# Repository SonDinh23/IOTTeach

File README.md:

# IOTTeach

<div align="center">

### Modular IoT Learning & Test Kit

<sub>IOTTeach v1.0 — Top side (above) · Bottom side (below)</sub>

<br/><br/>

</div>

---

## Table of Contents

| Section | Description |
|---------|-------------|
| About | Overview and intent |
| Hardware Overview | Technical summary |
| Key Features | Highlights and educational notes |
| Block Diagram | System block diagram |
| Getting Started | Quick start and assembly checklist |
| Lab Scenarios | Suggested exercises by level |
| License | License guidance |

---

## About

IOTTeach is a detachable plug-in kit designed for hands-on learning, quick hardware validation, and classroom labs. It exposes common peripherals (relays, RGB/status LEDs, buzzer) and standard 2.54 mm headers for power, analog, and digital lines so students and developers can prototype with any MCU or SBC without soldering a custom shield.

Design philosophy: Bring Your Own MCU — connect any microcontroller (ESP32, STM32, Arduino, Raspberry Pi Pico, etc.) using Dupont wires.

---

## Hardware Overview

| Component | Detail |
|:--------:|:------|
| Power | DC jack (DC-005) + terminal block → TPS54202 buck converter → 3.3V/5V rail |
| GPIO Headers | Digital 1×10 · Digital 1×8 · Analog 1×6 · Power header (pitch 2.54 mm) |
| LED Indicators | 2× WS2812B RGB, discrete status LEDs (green/yellow/red) |
| Audio | Piezo buzzer (CMT-8530S-SMT), PWM capable |
| Relays | 2× Omron G5NB SPST relays, driven via SS8050 transistors |
| Protection | SS34 Schottky diodes for flyback, decoupling capacitors and input protection |
| Project Files | KiCad project and production outputs under `hardware/IOT1_V1.0/production/` |

### Core Components (summary)

• TPS54202DDC — Buck converter (3.3V, up to ~2A)

• WS2812B (×2) — Addressable RGB LEDs for visual feedback

• Omron G5NB Relays (×2) — SPST relays for switching experiments (observe safety limits)

• CMT-8530S-SMT — Piezo buzzer for audible signals

• SS8050 (×3) — NPN transistors as relay drivers

• SS34 (×4) — Schottky diodes for flyback/protection

---

## Key Features

### Modular & MCU-Agnostic

- Plug-and-play design: wire any MCU to the headers — no soldering required.
- Standard 2.54 mm pitch makes connecting and swapping modules fast and reliable.

### Education-Focused Layout

- Clear, labeled headers and wide component spacing for easy probing with oscilloscopes and logic analyzers.
- Progressive learning path: LEDs → switches → buzzer → relays → RGB, enabling stepwise lab exercises.

### Fabrication-Ready

- Complete production artifacts included: BOM, pick-and-place, netlist and KiCad project files.
- Files are in `hardware/IOT1_V1.0/production/` for easy handoff to PCB fabs and assemblers.

---

## Block Diagram

```
                              ┌─────────────────────────────────────┐
                              │          IOTTeach Board             │
                              └─────────────────────────────────────┘
                                              │
        ┌───────────────────────────────────────────────────────────────────┐
        │                                                                   │
        ▼                                                                   ▼
┌───────────────┐                                               ┌───────────────┐
│  POWER INPUT  │                                               │   MCU SIDE    │
│───────────────│                                               │───────────────│
│ • DC Jack     │                                               │ • Digital I/O │
│ • Terminal    │──► TPS54202 ──► 3.3V/5V Rail ──►             │ • Analog In   │
│   Block       │       Buck                                    │ • Power       │
└───────────────┘                                               └───────┬───────┘
                                                                        │
        ┌───────────────────────────────────────────────────────────────┘
        │
        ▼
┌─────────────────────────────────────────────────────────────────────────────┐
│                              PERIPHERALS                                     │
├─────────────────┬─────────────────┬─────────────────┬───────────────────────┤
│   VISUAL        │   AUDIO         │   ACTUATORS     │   INPUTS              │
├─────────────────┼─────────────────┼─────────────────┼───────────────────────┤
│ • 2× WS2812B    │ • Piezo Buzzer  │ • 2× SPST Relay │ • 2× Tactile Switch   │
│ • Status LEDs   │   (PWM tone)    │   (5A/250VAC)   │                       │
│                 │                 │ • SS34 Flyback  │                       │
└─────────────────┴─────────────────┴─────────────────┴───────────────────────┘
```

---

## Getting Started

### Prerequisites

- KiCad 7+ to view or edit the PCB project
- Any MCU board (ESP32, Arduino, STM32 Nucleo, Raspberry Pi Pico, etc.)
- Dupont jumper wires (Female-Female or Male-Female)

### Quick Start

```powershell
# Clone repository
git clone https://github.com/SonDinh23/IOTTeach.git
cd IOTTeach

# Open the KiCad project:
# File → Open Project → hardware/IOT1_V1.0/IOT1_V1.0.kicad_pro
```

### Recommended Assembly Order

1. Power stage: TPS54202, inductor, input/output capacitors, SS34 diodes
2. Install pin headers (all GPIO/power headers)
3. Passive components (resistors, caps)
4. Semiconductors (transistors, diodes, LEDs)
5. Modules and larger components (relays, buzzer, WS2812B)
6. Connectors and switches (DC jack, terminal blocks)

### First Power-On Checklist

- Verify no short between VCC and GND before powering
- Apply input power via DC jack (7–12 V recommended)
- Measure output rail (3.3V or 5V depending on configuration)
- Confirm power indicator LED lights up
- Connect MCU and run a basic LED blink test

---

## Lab Scenarios (Suggested Exercises)

### Level 1 — Beginner

- LED Blink: control a status LED (digital output)
- Button Read: read a tactile switch (digital input, pull-up)
- Buzzer Tone: generate tones using PWM (basic PWM)

### Level 2 — Intermediate

- RGB Effects: drive WS2812B for color patterns (NeoPixel protocol)
- Relay Timer: implement a timed relay control routine (timers/state machine)
- LED Patterns: create multi-LED sequences and animations (arrays/loops)

### Level 3 — Advanced

- Alarm System: integrate buzzer, RGB, and relay for a simulated alarm
- Power Profiling: measure board current under different loads (instrumentation)
- Remote Control: connect an MCU with Wi-Fi/BLE to control relays (networking)

---

## License

This project is presented as Open Hardware. Please add a specific license (for example, CERN-OHL, TAPR-OHL, or CC-BY-SA) to the repository before distributing manufacturing files or derivative works.

---

## Thanks

Thank you for exploring IOTTeach. Contributions, documentation improvements, and lab material suggestions are welcome — open an issue or submit a pull request.

<div align="center">

**[Back to Top](#iotteach)**

</div>

| Tính năng | Mô tả |
|-----------|-------|
| **MCU Agnostic** | Tương thích ESP32, STM32, Arduino, Raspberry Pi Pico, v.v. |
| **Plug & Play** | Kết nối nhanh qua dây Dupont, không cần hàn |
| **Header chuẩn** | Pitch 2.54mm phổ biến, dễ tìm phụ kiện |

### 📚 Education-Focused

| Tính năng | Mô tả |
|-----------|-------|
| **Clear Layout** | Component spacing rộng, dễ đo đạc oscilloscope |
| **Labeled Headers** | Đánh dấu rõ ràng chức năng từng chân |
| **Gradual Learning** | Từ LED → Switch → Buzzer → Relay → RGB |

### �icing Fabrication-Ready

| Tài liệu | Đường dẫn |
|----------|-----------|
| **Schematic** | `hardware/IOT1_V1.0/IOT1_V1.0.kicad_sch` |
| **PCB Layout** | `hardware/IOT1_V1.0/IOT1_V1.0.kicad_pcb` |
| **3D Model** | `hardware/IOT1_V1.0/IOT1_V1.0.step` |
| **BOM** | `hardware/IOT1_V1.0/production/bom.csv` |
| **Pick & Place** | `hardware/IOT1_V1.0/production/positions.csv` |

---

## 📊 Block Diagram

```
                              ┌─────────────────────────────────────┐
                              │          IOTTeach Board             │
                              └─────────────────────────────────────┘
                                              │
        ┌───────────────────────────────────────────────────────────────────┐
        │                                                                   │
        ▼                                                                   ▼
┌───────────────┐                                               ┌───────────────┐
│  POWER INPUT  │                                               │   MCU SIDE    │
│───────────────│                                               │───────────────│
│ • DC Jack     │                                               │ • Digital I/O │
│ • Terminal    │──► TPS54202 ──► 3.3V/5V Rail ──►             │ • Analog In   │
│   Block       │       Buck                                    │ • Power       │
└───────────────┘                                               └───────┬───────┘
                                                                        │
        ┌───────────────────────────────────────────────────────────────┘
        │
        ▼
┌─────────────────────────────────────────────────────────────────────────────┐
│                              PERIPHERALS                                     │
├─────────────────┬─────────────────┬─────────────────┬───────────────────────┤
│   💡 VISUAL     │   🔊 AUDIO      │   ⚙️ ACTUATOR   │   🎛️ INPUT            │
├─────────────────┼─────────────────┼─────────────────┼───────────────────────┤
│ • 2× WS2812B    │ • Piezo Buzzer  │ • 2× SPST Relay │ • 2× Tactile Switch   │
│ • 2× LED Green  │   (PWM tone)    │   (5A/250VAC)   │                       │
│ • 1× LED Yellow │                 │ • SS34 Flyback  │                       │
│ • 3× LED Red    │                 │                 │                       │
└─────────────────┴─────────────────┴─────────────────┴───────────────────────┘
```

---

## 🚀 Getting Started

### Prerequisites

- **KiCad 7+** để xem/chỉnh sửa thiết kế
- **MCU board** bất kỳ (ESP32, Arduino Uno, STM32 Nucleo, etc.)
- **Dây Dupont** Female-Female hoặc Male-Female

### Quick Start

```bash
# 1. Clone repository
git clone https://github.com/SonDinh23/IOTTeach.git
cd IOTTeach

# 2. Mở project KiCad
# File → Open Project → hardware/IOT1_V1.0/IOT1_V1.0.kicad_pro
```

### Assembly Order (Khuyến nghị)

| Bước | Thành phần | Ghi chú |
|:----:|------------|---------|
| 1️⃣ | **Power Stage** | TPS54202, inductor L1, capacitors, SS34 diodes |
| 2️⃣ | **Headers** | Tất cả pin headers (J1-J14) |
| 3️⃣ | **Passives** | Resistors, capacitors còn lại |
| 4️⃣ | **Semiconductors** | Transistors SS8050, LEDs |
| 5️⃣ | **Modules** | Relays, buzzer, WS2812B |
| 6️⃣ | **Connectors** | DC jack, terminal blocks, switches |

### First Power-On Checklist

- [ ] Kiểm tra ngắn mạch giữa VCC-GND trước khi cấp nguồn
- [ ] Cấp nguồn qua DC jack (7-12V recommended)
- [ ] Đo điện áp output rail (3.3V hoặc 5V tùy config)
- [ ] LED power indicator sáng
- [ ] Kết nối MCU và test blink LED

---

## 🧪 Lab Scenarios

### 🟢 Level 1: Beginner

| Bài lab | Mô tả | Kỹ năng |
|---------|-------|---------|
| **LED Blink** | Điều khiển LED đơn ON/OFF | Digital Output |
| **Button Read** | Đọc trạng thái nút nhấn | Digital Input, Pull-up |
| **Buzzer Tone** | Tạo âm thanh với tần số khác nhau | PWM basics |

### 🟡 Level 2: Intermediate

| Bài lab | Mô tả | Kỹ năng |
|---------|-------|---------|
| **RGB Rainbow** | Hiệu ứng cầu vồng với WS2812B | NeoPixel protocol |
| **Relay Timer** | Bật/tắt relay theo thời gian | Timing, State machine |
| **Multi-LED Pattern** | Đèn chạy đuổi, hiệu ứng | Arrays, Loops |

### 🔴 Level 3: Advanced

| Bài lab | Mô tả | Kỹ năng |
|---------|-------|---------|
| **Smart Alarm** | Hệ thống báo động: buzzer + LED + relay | System integration |
| **Power Profiling** | Đo dòng tiêu thụ ở các chế độ | Instrumentation |
| **IoT Control** | Điều khiển relay qua WiFi/BLE | Networking |

---

## 📜 License

Dự án này được phát hành dưới dạng **Open Hardware**.

> ⚠️ Vui lòng thêm license cụ thể (CERN-OHL, TAPR-OHL, hoặc CC-BY-SA) trước khi phân phối thiết kế.

---

## 🙏 Thanks

Cảm ơn bạn đã quan tâm đến **IOTTeach**!

Mọi góp ý về thiết kế, tài liệu hướng dẫn, hoặc ý tưởng bài thực hành đều được hoan nghênh.

<div align="center">

**[⬆ Back to Top](#iotteach)**

</div>

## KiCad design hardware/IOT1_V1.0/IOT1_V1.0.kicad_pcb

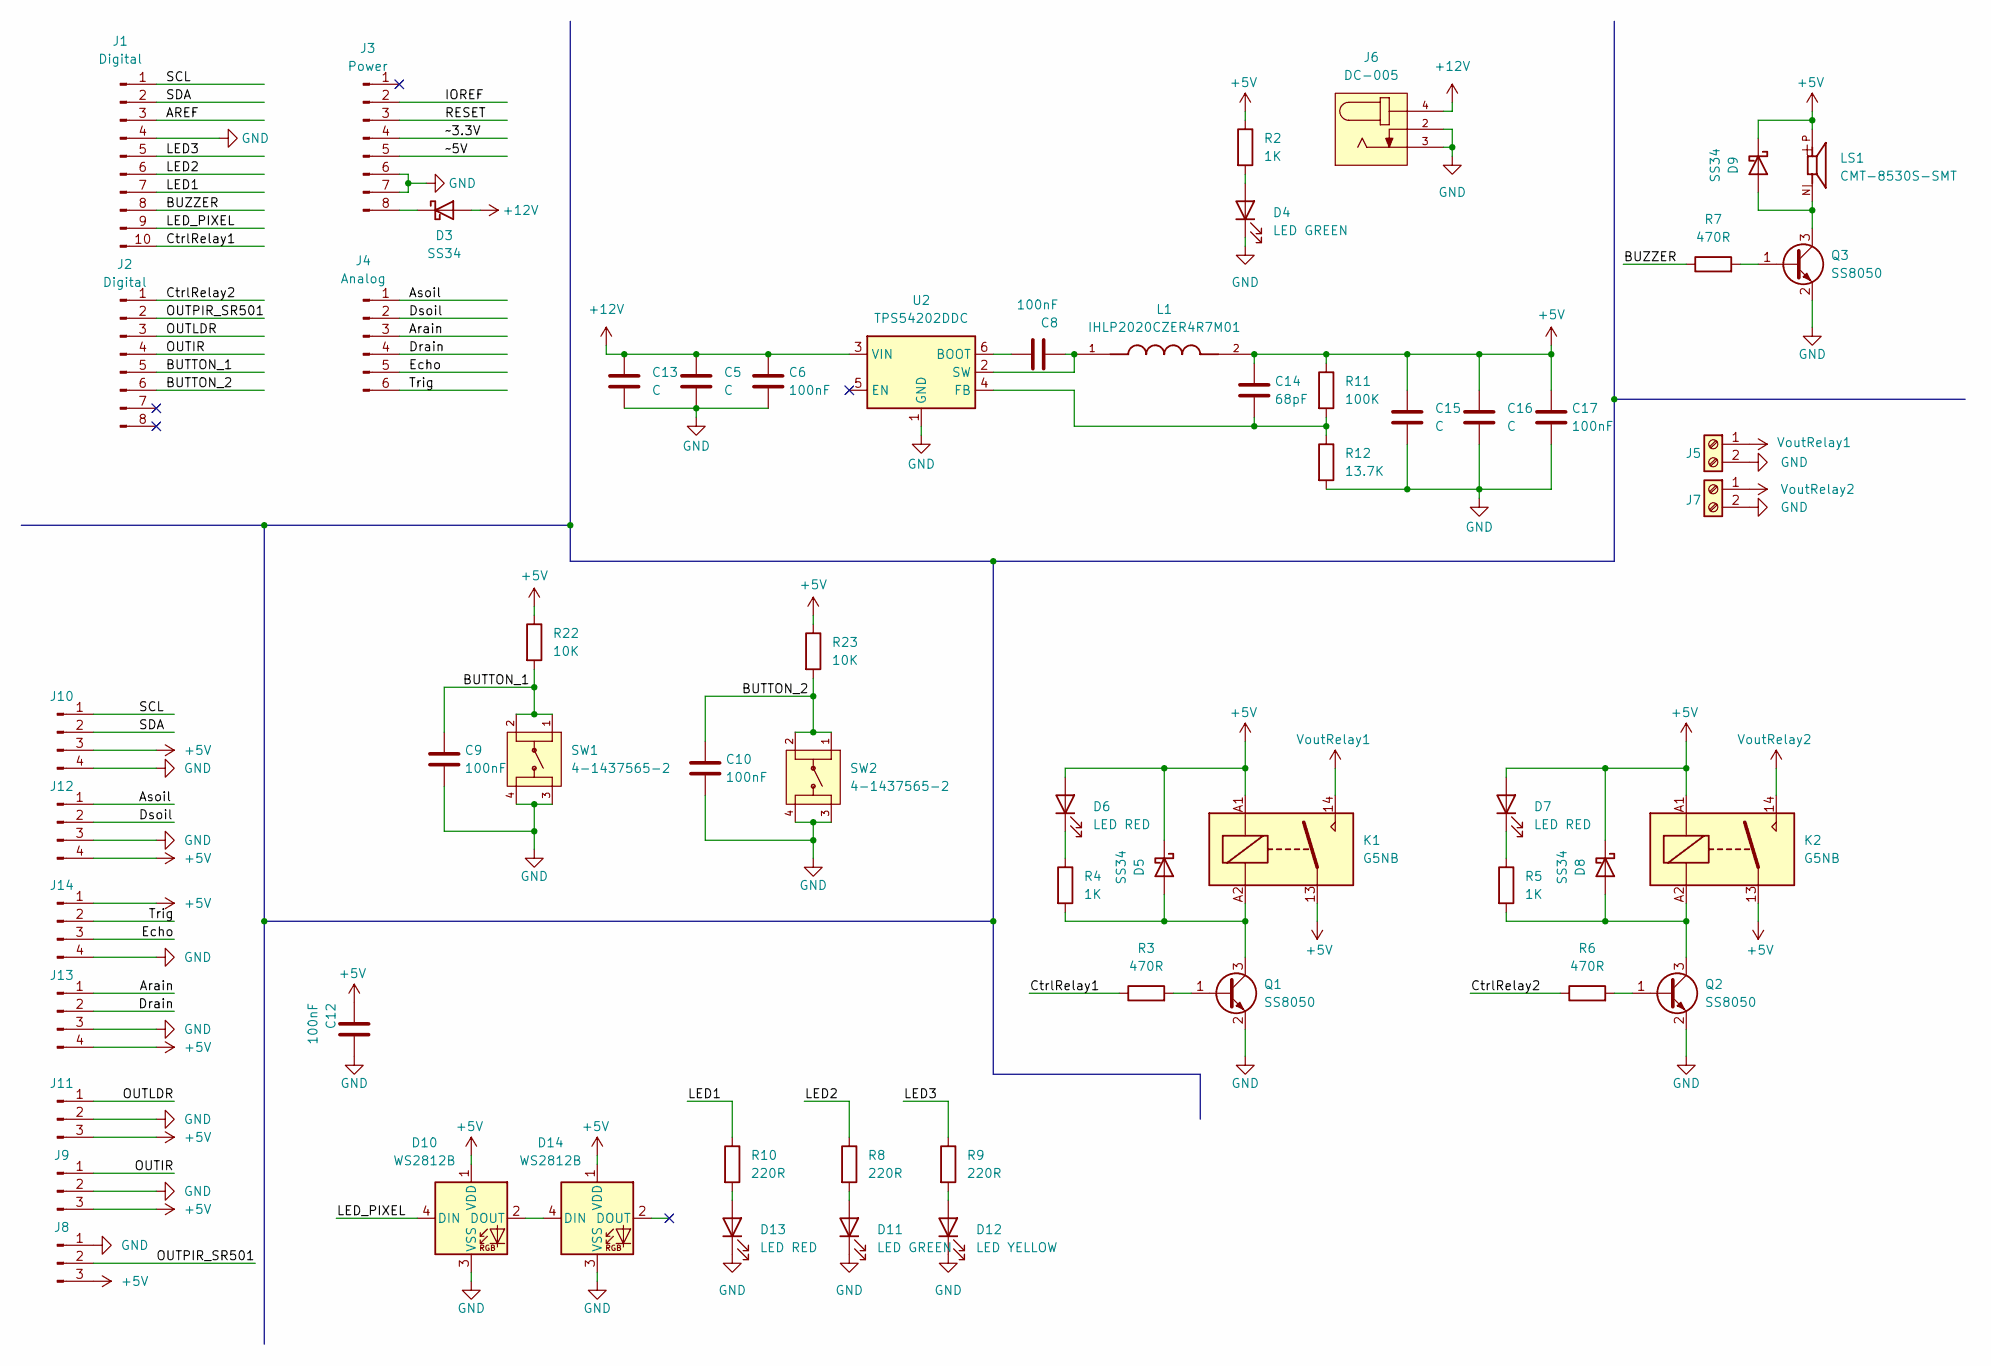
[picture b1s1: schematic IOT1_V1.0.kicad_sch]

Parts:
C5, C13, C15, C16: C; C_1210_3225Metric
C6, C8, C9, C10, C12, C17: 100nF; C_0603_1608Metric_Pad1.08x0.95mm_HandSolder
C14: 68pF; C_0603_1608Metric_Pad1.08x0.95mm_HandSolder
D3, D5, D8, D9: SS34; D_SMA
D4, D11: LED GREEN; LED_0805_2012Metric
D6, D7, D13: LED RED; LED_0805_2012Metric
D10, D14: WS2812B; LED_WS2812B_PLCC4_5.0x5.0mm_P3.2mm
D12: LED YELLOW; LED_0805_2012Metric
J1: Digital; PinHeader_1x10_P2.54mm_Vertical_SMD_Pin1Right
J2: Digital; PinHeader_1x08_P2.54mm_Vertical_SMD_Pin1Right
J3: Power; PinHeader_1x08_P2.54mm_Vertical_SMD_Pin1Right
J4: Analog; PinHeader_1x06_P2.54mm_Vertical_SMD_Pin1Right
J5, J7: Screw_Terminal_01x02; TerminalBlock_Xinya_XY308-2.54-2P_1x02_P2.54mm_Horizontal
J6: DC-005; NINIGI_DC-005
J8, J9, J11: Conn_01x03_Pin; PinHeader_1x03_P2.54mm_Horizontal
J10, J12, J13, J14: Conn_01x04_Pin; PinHeader_1x04_P2.54mm_Horizontal
K1, K2: G5NB; Relay_SPST_Omron_G5NB
L1: IHLP2020CZER4R7M01; INDM5451X300N; PARTREV 08-Jan-2024
LS1: CMT-8530S-SMT; CUI_CMT-8530S-SMT
Q1, Q2, Q3: SS8050; SOT-23
R2, R4, R5: 1K; R_0603_1608Metric
R3, R6, R7: 470R; R_0603_1608Metric
R8, R9, R10: 220R; R_0603_1608Metric
R11: 100K; R_0603_1608Metric
R12: 13.7K; R_0603_1608Metric
R22, R23: 10K; C_0603_1608Metric
SW1, SW2: 4-1437565-2; SW_4-1437565-2; PARTREV V
U2: TPS54202DDC; SOT-23-6

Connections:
+5V: C12.2, C14.1, C15.1, C16.1, C17.1, D5.1 (K), D6.2 (A), D7.2 (A), D8.1 (K), D9.1 (K), D10.1 (VDD), D14.1 (VDD), J8.3, J9.3, J10.3, J11.3, J12.4, J13.4, J14.1, K1.13, K1.A1, K2.13, K2.A1, L1.2, LS1.P, R2.1, R11.1, R22.1, R23.1
+12V: C5.1, C6.1, C13.1, D3.2 (A), J6.4, U2.3 (VIN)
/AREF: J1.3
/Arain: J4.3, J13.1
/Asoil: J4.1, J12.1
/BUTTON_1: C9.1, J2.5, R22.2, SW1.1, SW1.2
/BUTTON_2: C10.1, J2.6, R23.2, SW2.1, SW2.2
/BUZZER: J1.8, R7.1
/CtrlRelay1: J1.10, R3.1
/CtrlRelay2: J2.1, R6.1
/Drain: J4.4, J13.2
/Dsoil: J4.2, J12.2
/Echo: J4.5, J14.3
/IOREF: J3.2
/LED1: J1.7, R10.1
/LED2: J1.6, R8.1
/LED3: J1.5, R9.1
/LED_PIXEL: D10.4 (DIN), J1.9
/OUTIR: J2.4, J9.1
/OUTLDR: J2.3, J11.1
/OUTPIR_SR501: J2.2, J8.2
/RESET: J3.3
/SCL: J1.1, J10.1
/SDA: J1.2, J10.2
/Trig: J4.6, J14.2
/~3.3V: J3.4
/~5V: J3.5
GND: C5.2, C6.2, C9.2, C10.2, C12.1, C13.2, C15.2, C16.2, C17.2, D4.1 (K), D10.3 (VSS), D11.1 (K), D12.1 (K), D13.1 (K), D14.3 (VSS), J1.4, J3.6, J3.7, J5.2, J6.2, J6.3, J7.2, J8.1, J9.2, J10.4, J11.2, J12.3, J13.3, J14.4, Q1.2 (E), Q2.2 (E), Q3.2 (E), R12.2, SW1.3, SW1.4, SW2.3, SW2.4, U2.1 (GND)
unnamed: D3.1 (K), J3.8
unnamed: D4.2 (A), R2.2
unnamed: D5.2 (A), K1.A2, Q1.3 (C), R4.2
unnamed: D6.1 (K), R4.1
unnamed: D7.1 (K), R5.1
unnamed: D8.2 (A), K2.A2, Q2.3 (C), R5.2
unnamed: D9.2 (A), LS1.N, Q3.3 (C)
unnamed: D10.2 (DOUT), D14.4 (DIN)
unnamed: D11.2 (A), R8.2
unnamed: D12.2 (A), R9.2
unnamed: D13.2 (A), R10.2
unnamed: Q1.1 (B), R3.2
unnamed: Q2.1 (B), R6.2
unnamed: Q3.1 (B), R7.2
unnamed: C8.1, U2.6 (BOOT)
unnamed: C14.2, R11.2, R12.1, U2.4 (FB)
unnamed: C8.2, L1.1, U2.2 (SW)
VoutRelay1: J5.1, K1.14
VoutRelay2: J7.1, K2.14

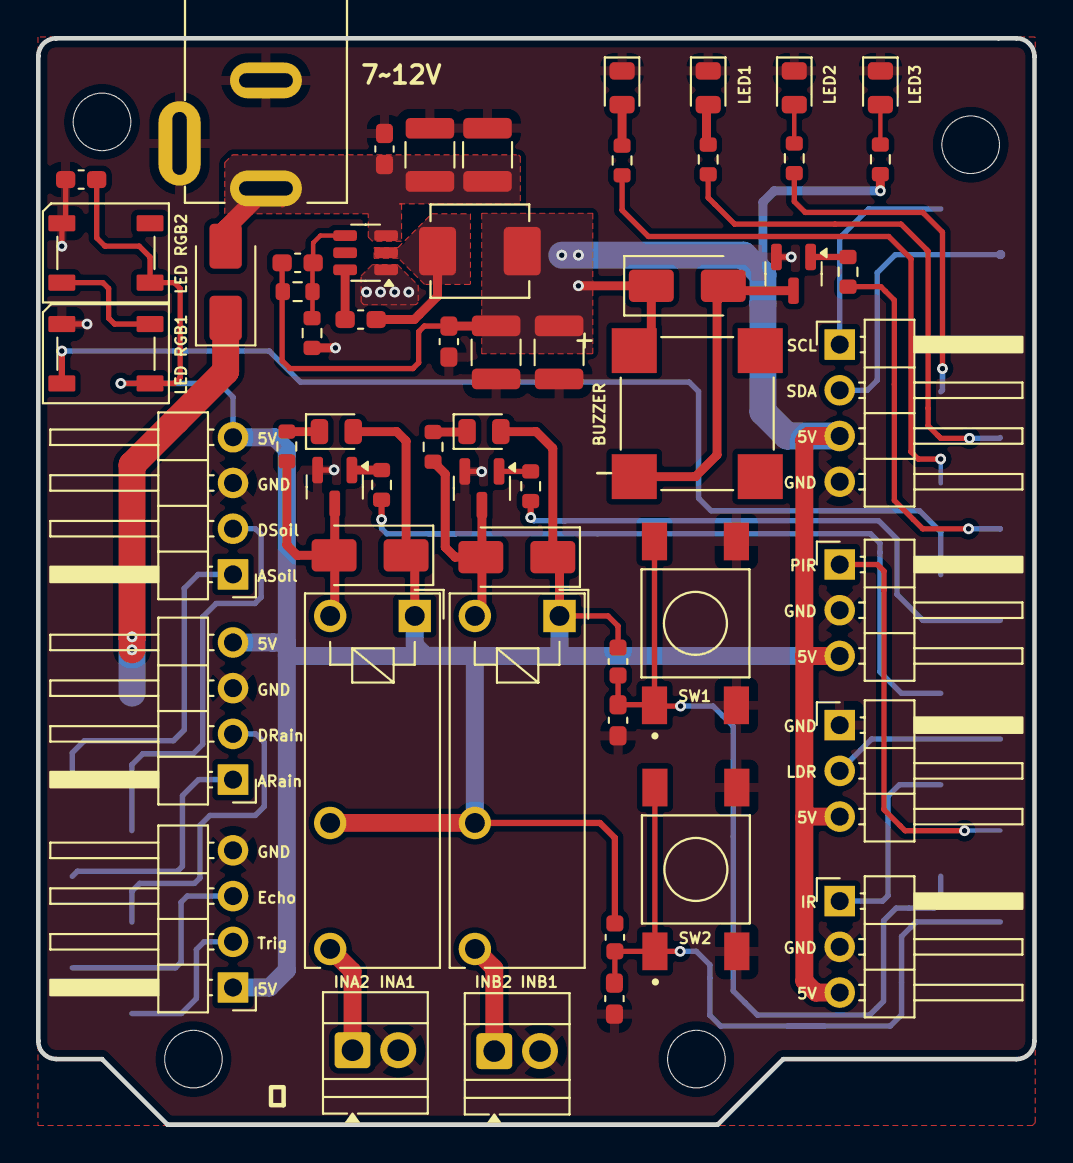
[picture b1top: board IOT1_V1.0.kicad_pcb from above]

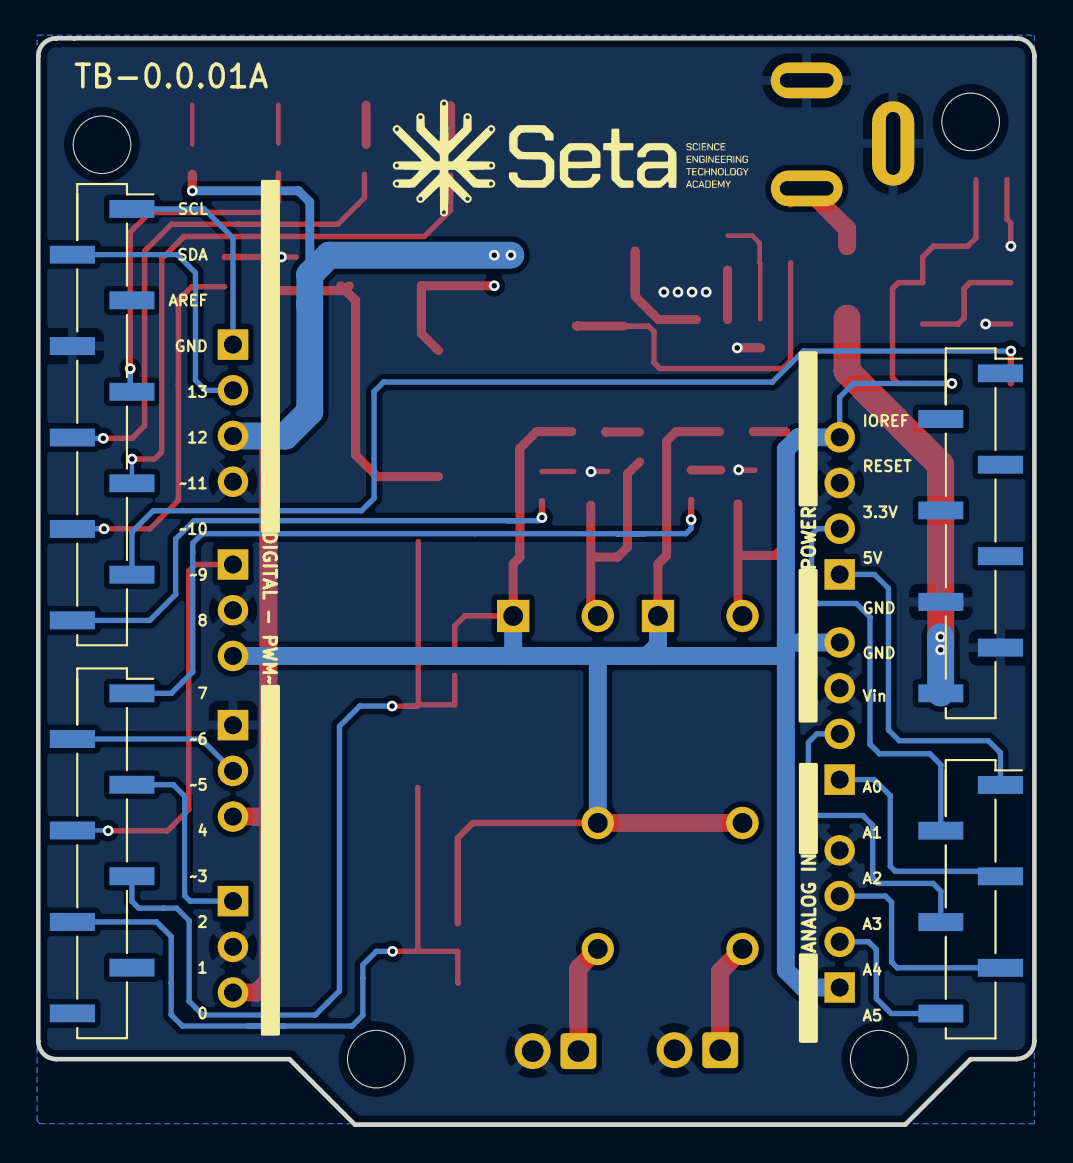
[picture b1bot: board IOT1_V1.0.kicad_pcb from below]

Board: 2 copper layers, 55.3 x 60.4 mm, 60 parts (4 on the bottom side), 42 nets.

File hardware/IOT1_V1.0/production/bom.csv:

Designator,Footprint,Quantity,Value,LCSC Part #
"C10, C12, C17, C6, C8, C9",0603,6,100nF,
"C13, C15, C16, C5",1210,4,C,
C14,0603,1,68pF,
"D10, D14",LED_WS2812B_PLCC4_5.0x5.0mm_P3.2mm,2,WS2812B,
"D11, D4",0805,2,LED GREEN,
D12,0805,1,LED YELLOW,
"D13, D6, D7",0805,3,LED RED,
"D3, D5, D8, D9",D_SMA,4,SS34,
J1,PinHeader_1x10_P2.54mm_Vertical_SMD_Pin1Right,1,Digital,
"J10, J12, J13, J14",PinHeader_1x04_P2.54mm_Horizontal,4,Conn_01x04_Pin,
"J11, J8, J9",PinHeader_1x03_P2.54mm_Horizontal,3,Conn_01x03_Pin,
J2,PinHeader_1x08_P2.54mm_Vertical_SMD_Pin1Right,1,Digital,
J3,PinHeader_1x08_P2.54mm_Vertical_SMD_Pin1Right,1,Power,
J4,PinHeader_1x06_P2.54mm_Vertical_SMD_Pin1Right,1,Analog,
"J5, J7",TerminalBlock_Xinya_XY308-2.54-2P_1x02_P2.54mm_Horizontal,2,Screw_Terminal_01x02,
J6,NINIGI_DC-005,1,DC-005,
"K1, K2",Relay_SPST_Omron_G5NB,2,G5NB,
L1,INDM5451X300N,1,IHLP2020CZER4R7M01,
LS1,CUI_CMT-8530S-SMT,1,CMT-8530S-SMT,
"Q1, Q2, Q3",SOT-23,3,SS8050,
"R10, R8, R9",0603,3,220R,
R11,0603,1,100K,
R12,0603,1,13.7K,
"R2, R4, R5",0603,3,1K,
"R22, R23",0603,2,10K,
"R3, R6, R7",0603,3,470R,
"SW1, SW2",SW_4-1437565-2,2,4-1437565-2,
U2,SOT-23-6,1,TPS54202DDC,

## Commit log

2025-12-09 feature: add hardware board IOT1
